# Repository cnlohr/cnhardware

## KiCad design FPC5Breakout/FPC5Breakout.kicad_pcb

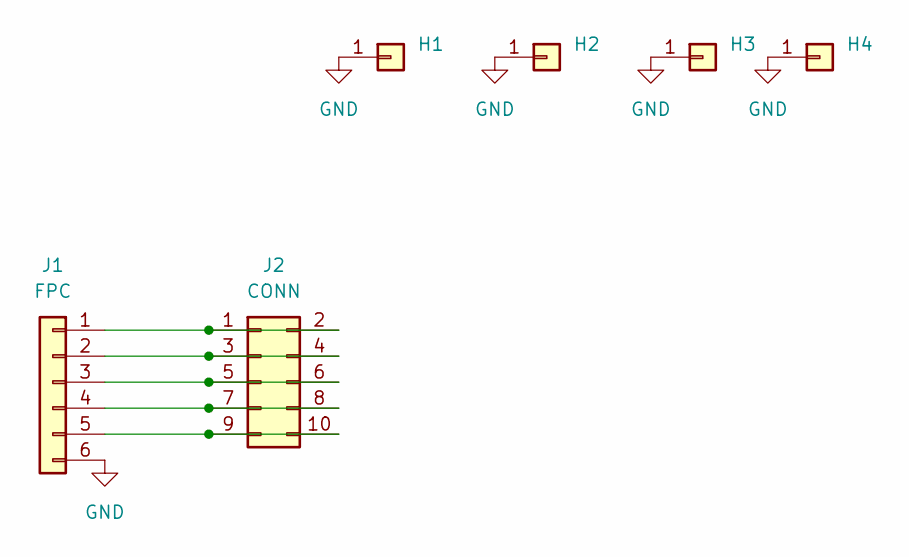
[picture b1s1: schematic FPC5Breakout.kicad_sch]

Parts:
H1, H2, H3, H4: MountingHole_3.2mm_M3_ISO14580_Pad
J1: FPC; XCB-FPC-DS-05-0.5mm; LCSC C2880762
J2: CONN; PinHeader_2x05_P2.54mm_Vertical; LCSC C124387

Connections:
GND: H1.1, H2.1, H3.1, H4.1, J1.6
unnamed: J1.1, J2.1, J2.2
unnamed: J1.2, J2.3, J2.4
unnamed: J1.3, J2.5, J2.6
unnamed: J1.4, J2.7, J2.8
unnamed: J1.5, J2.9, J2.10

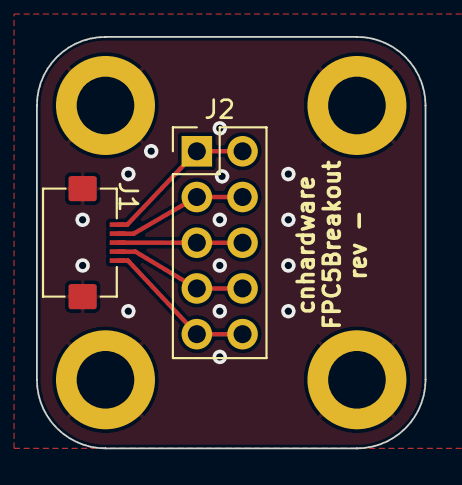
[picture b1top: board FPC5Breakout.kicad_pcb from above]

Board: 2 copper layers, 21.6 x 22.9 mm, 6 parts (0 on the bottom side), 6 nets.

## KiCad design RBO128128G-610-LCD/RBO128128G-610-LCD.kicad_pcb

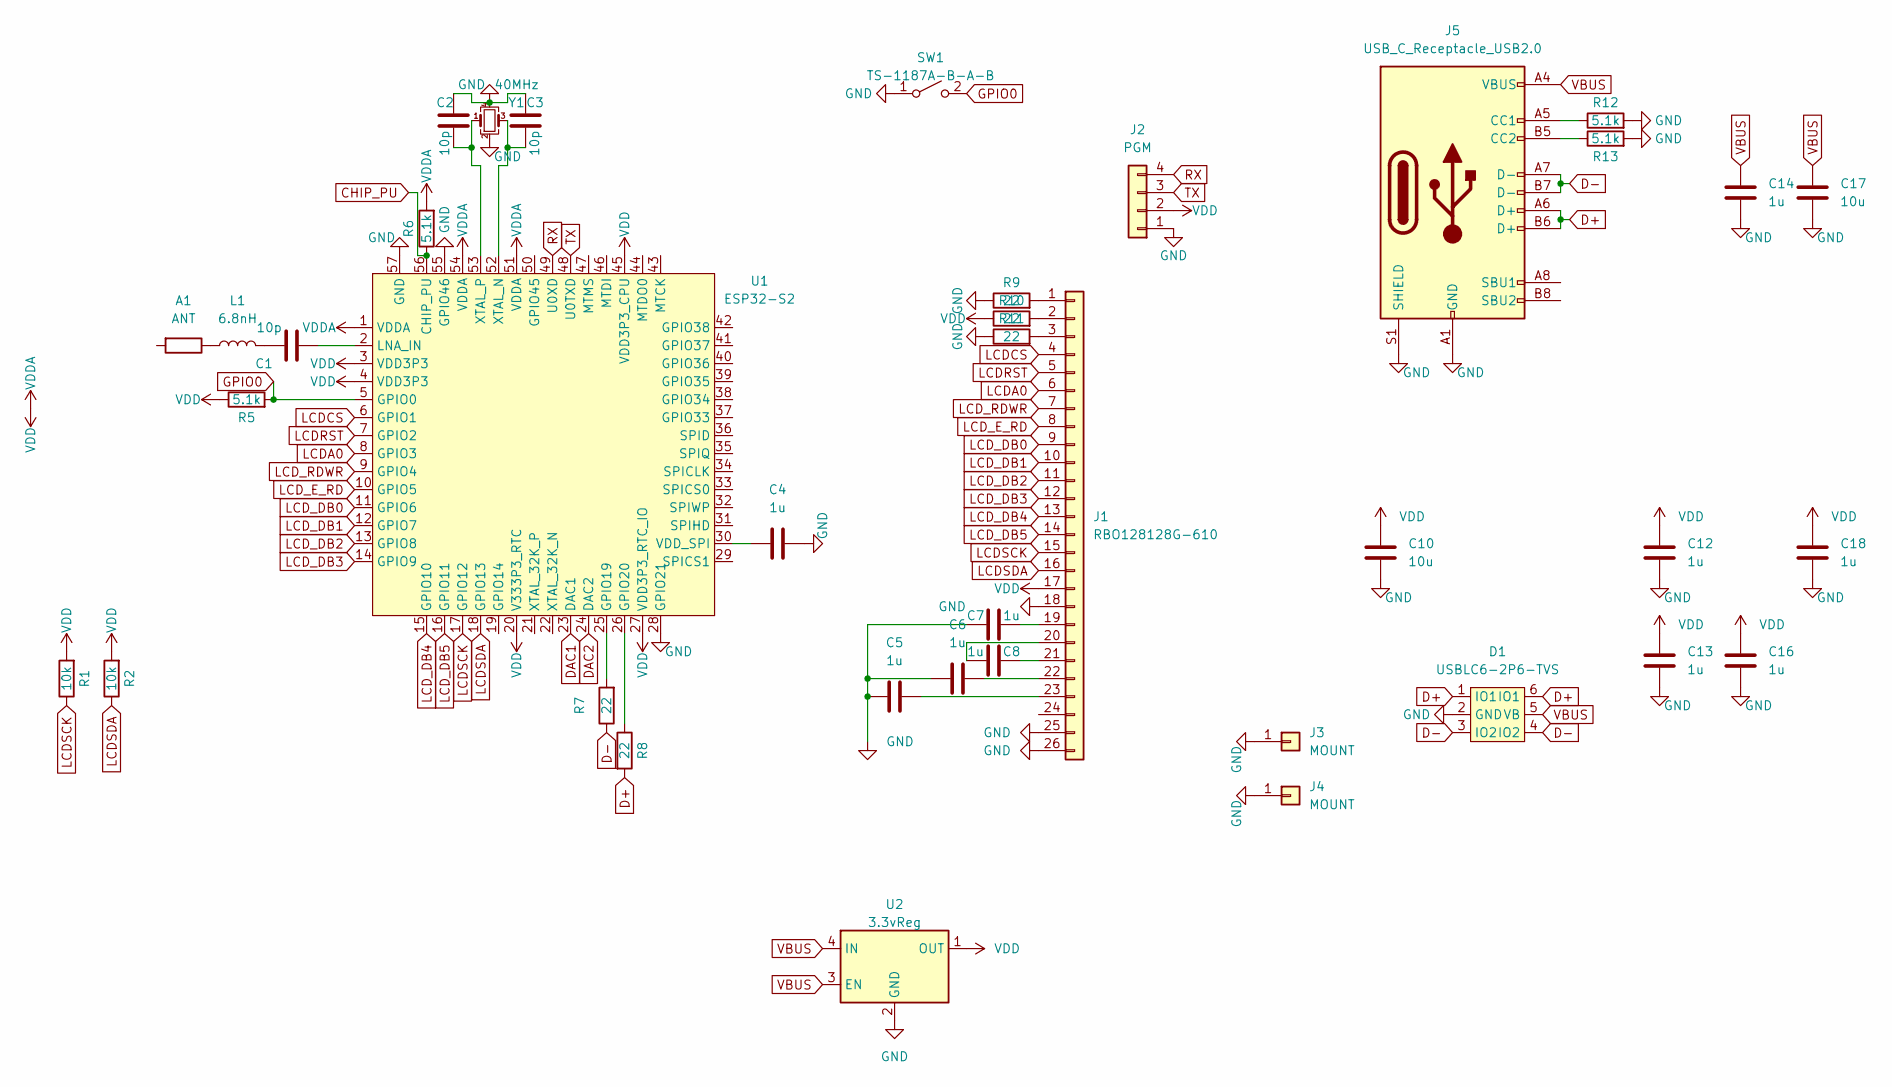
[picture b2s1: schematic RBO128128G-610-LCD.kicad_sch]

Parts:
A1: ANT; R_1206_3216Metric; LCSC C127629
C1, C2, C3: 10p; C_0402_1005Metric; LCSC C106199
C4, C5, C6, C7, C8, C12, C13, C14, C16, C18: 1u; C_0402_1005Metric; LCSC C106254
C10, C17: 10u; C_0603_1608Metric; LCSC C18800
D1: USBLC6-2P6-TVS; SOT-666; LCSC C2827693
J1: RBO128128G-610
J2: PGM; PinHeader_1x04_P2.54mm_Vertical; LCSC NP
J3, J4: MOUNT; MountingHole_2.2mm_M2_DIN965_Pad
J5: USB_C_Receptacle_USB2.0; USB_C_Receptacle_HRO_TYPE-C-31-M-12; LCSC C2765186
L1: 6.8nH; L_0402_1005Metric; LCSC C77110
R1, R2: 10k; R_0402_1005Metric; LCSC C144807
R5, R6, R12, R13: 5.1k; R_0402_1005Metric; LCSC C105872
R7, R8, R9, R10, R11: 22; R_0402_1005Metric; LCSC C25092
SW1: TS-1187A-B-A-B; SW_SPST_TL3342; LCSC C318884
U1: ESP32-S2; ESP32S2; LCSC C2840995
U2: 3.3vReg; xdfn-reg; LCSC C81114
Y1: 40MHz; Crystal_SMD_2016-4Pin_2.0x1.6mm; LCSC C648970

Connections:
CHIP_PU: R6.1, U1.56 (CHIP_PU)
D+: D1.1 (IO1), D1.6 (IO1), J5.A6 (D+), J5.B6 (D+), R8.2
D-: D1.3 (IO2), D1.4 (IO2), J5.A7 (D-), J5.B7 (D-), R7.1
DAC1: U1.23 (DAC1)
DAC2: U1.24 (DAC2)
GND: C2.1, C3.1, C4.2, C5.1, C6.1, C7.1, C10.2, C12.2, C13.2, C14.1, C16.2, C17.2, C18.2, D1.2 (GND), J1.18, J1.25, J1.26, J2.1, J3.1, J4.1, J5.A1 (GND), J5.A12 (GND), J5.B1 (GND), J5.B12 (GND), J5.S1 (SHIELD), R9.1, R11.1, R12.2, R13.2, SW1.1 (A), U1.28 (GPIO21), U1.55 (GPIO46), U1.57 (GND), U2.2 (GND), U2.5 (GND), Y1.2, Y1.4
GPIO0: R5.2, SW1.2 (B), U1.5 (GPIO0)
LCDA0: J1.6, U1.8 (GPIO3)
LCDCS: J1.4, U1.6 (GPIO1)
LCDRST: J1.5, U1.7 (GPIO2)
LCDSCK: J1.15, R1.1, U1.17 (GPIO12)
LCDSDA: J1.16, R2.1, U1.18 (GPIO13)
LCD_DB0: J1.9, U1.11 (GPIO6)
LCD_DB1: J1.10, U1.12 (GPIO7)
LCD_DB2: J1.11, U1.13 (GPIO8)
LCD_DB3: J1.12, U1.14 (GPIO9)
LCD_DB4: J1.13, U1.15 (GPIO10)
LCD_DB5: J1.14, U1.16 (GPIO11)
LCD_E_RD: J1.8, U1.10 (GPIO5)
LCD_RDWR: J1.7, U1.9 (GPIO4)
unnamed: A1.1, L1.1
unnamed: C1.1, L1.2
unnamed: C1.2, U1.2 (LNA_IN)
unnamed: C2.2, U1.53 (XTAL_P), Y1.1
unnamed: C3.2, U1.52 (XTAL_N), Y1.3
unnamed: C4.1, U1.30 (VDD_SPI)
unnamed: C5.2, J1.23
unnamed: C6.2, J1.22
unnamed: C7.2, J1.19
unnamed: C8.1, J1.20
unnamed: C8.2, J1.21
unnamed: J1.1, R9.2
unnamed: J1.2, R10.2
unnamed: J1.3, R11.2
unnamed: J5.A5 (CC1), R12.1
unnamed: J5.B5 (CC2), R13.1
unnamed: R7.2, U1.25 (GPIO19)
unnamed: R8.1, U1.26 (GPIO20)
RX: J2.4, U1.49 (U0XD)
TX: J2.3, U1.48 (U0TXD)
VBUS: C14.2, C17.1, D1.5 (VB), J5.A4 (VBUS), J5.A9 (VBUS), J5.B4 (VBUS), J5.B9 (VBUS), U2.3 (EN), U2.4 (IN)
VDD: C10.1, C12.1, C13.1, C16.1, C18.1, J1.17, J2.2, R1.2, R2.2, R5.1, R6.2, R10.1, U1.1 (VDDA), U1.3 (VDD3P3), U1.4 (VDD3P3), U1.20 (V333P3_RTC), U1.27 (VDD3P3_RTC_IO), U1.45 (VDD3P3_CPU), U1.51 (VDDA), U1.54 (VDDA), U2.1 (OUT)

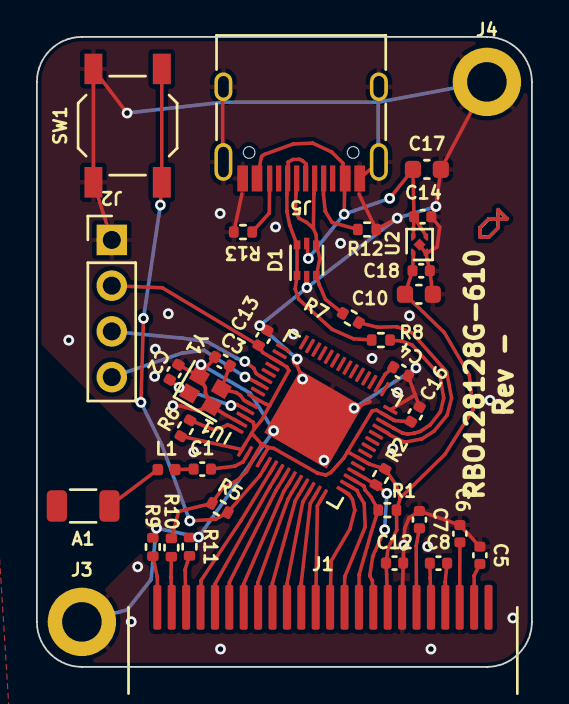
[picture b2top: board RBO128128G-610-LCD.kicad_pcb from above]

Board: 2 copper layers, 27.5 x 35.0 mm, 38 parts (0 on the bottom side), 40 nets.

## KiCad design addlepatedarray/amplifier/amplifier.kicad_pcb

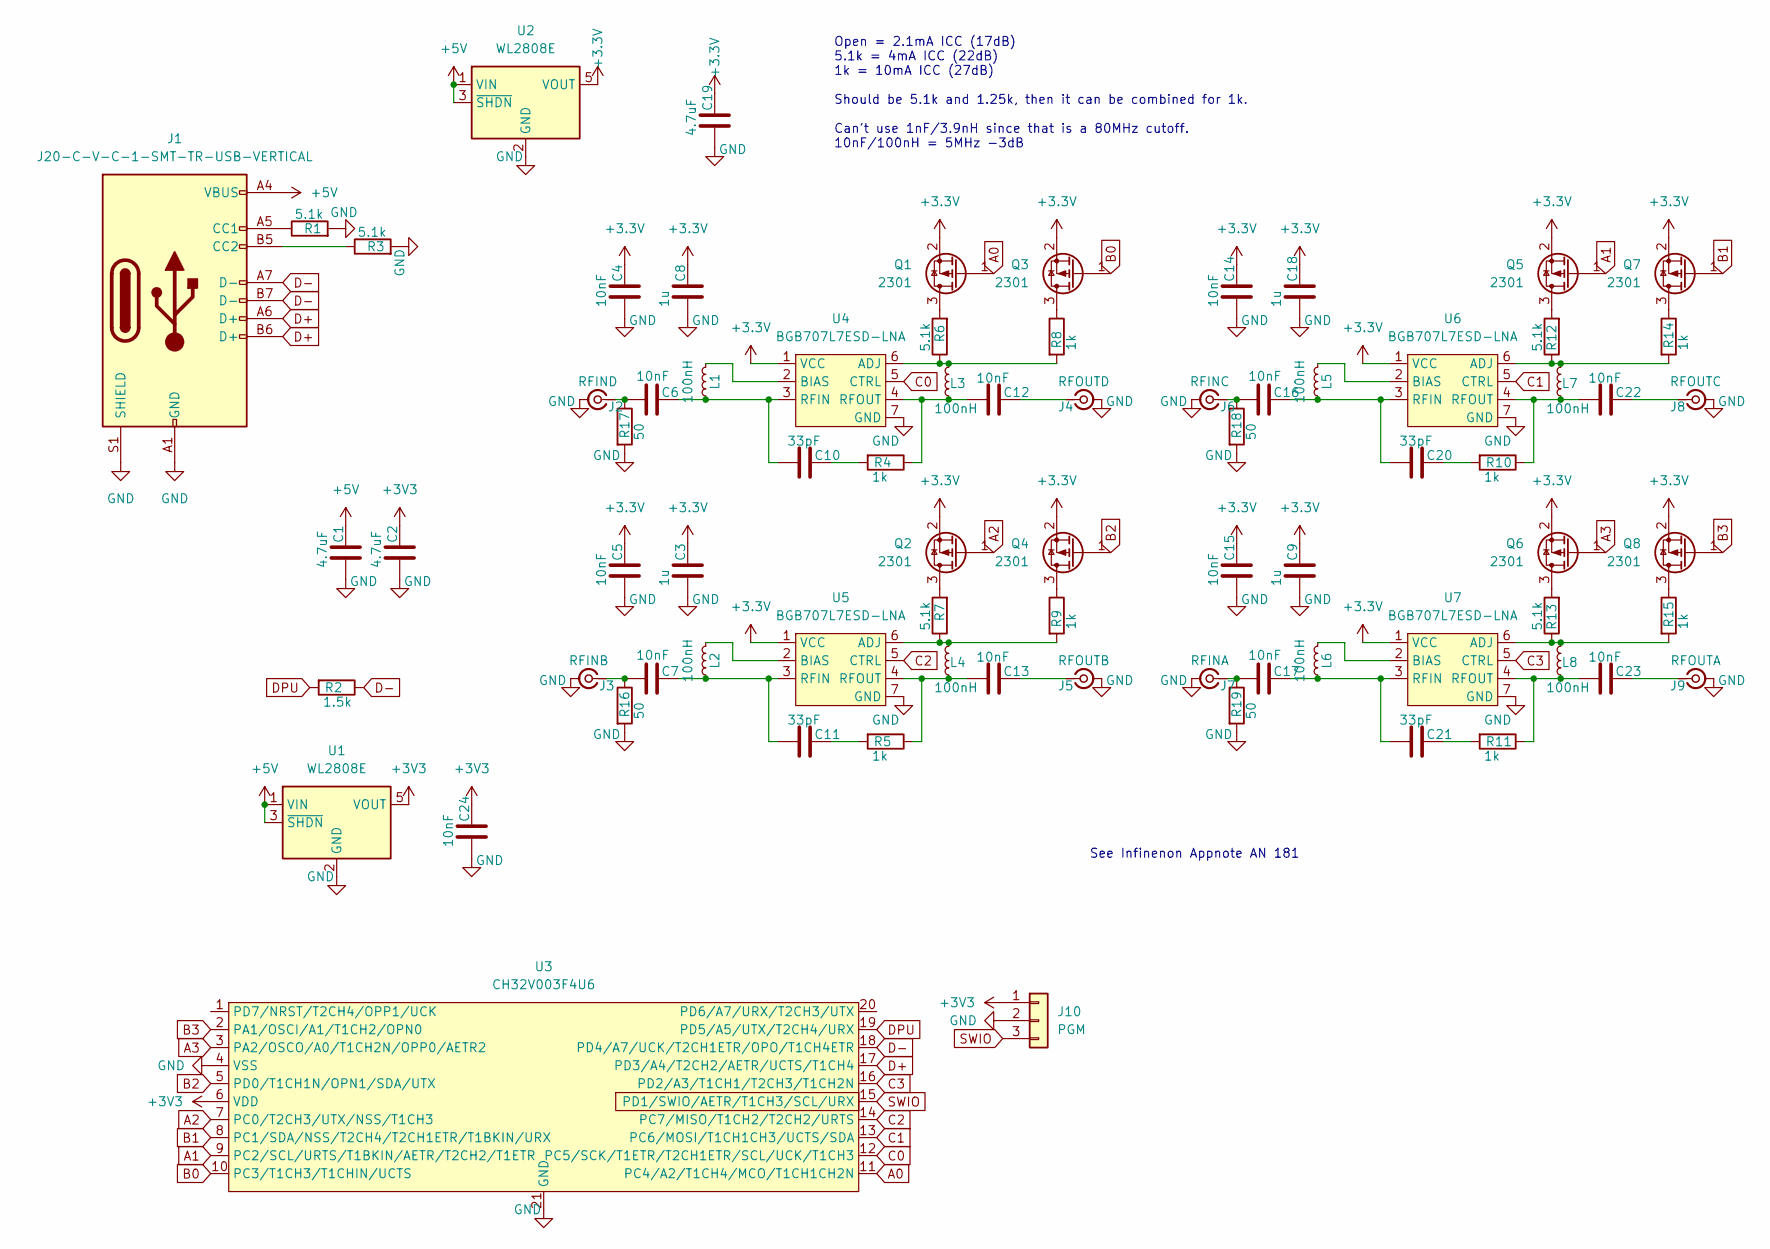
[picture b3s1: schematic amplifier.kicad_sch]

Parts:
C1, C2, C19: 4.7uF; R_0603_1608Metric; LCSC C19666
C3, C8, C9, C18: 1u; C_0402_1005Metric; LCSC C52923
C4, C5, C6, C7, C12, C13, C14, C15, C16, C17, C22, C23, C24: 10nF; C_0402_1005Metric; LCSC C15195
C10, C11, C20, C21: 33pF; C_0402_1005Metric; LCSC C1562
J1: J20-C-V-C-1-SMT-TR-USB-VERTICAL; LCSC NA
J2: RFIND; SMA_Amphenol_901-144_Vertical; LCSC C5301852
J3: RFINB; SMA_Amphenol_901-144_Vertical; LCSC C5301852
J4: RFOUTD; SMA_Amphenol_901-144_Vertical; LCSC C5301852
J5: RFOUTB; SMA_Amphenol_901-144_Vertical; LCSC C5301852
J6: RFINC; SMA_Amphenol_901-144_Vertical; LCSC C5301852
J7: RFINA; SMA_Amphenol_901-144_Vertical; LCSC C5301852
J8: RFOUTC; SMA_Amphenol_901-144_Vertical; LCSC C5301852
J9: RFOUTA; SMA_Amphenol_901-144_Vertical; LCSC C5301852
J10: PGM; PinHeader_1x03_P2.54mm_Vertical
L1, L2, L3, L4, L5, L6, L7, L8: 100nH; L_0402_1005Metric; LCSC C22726
Q1, Q2, Q3, Q4, Q5, Q6, Q7, Q8: 2301; SOT-23; LCSC C41384537
R1, R3, R6, R7, R12, R13: 5.1k; R_0402_1005Metric; LCSC C25905
R2: 1.5k; R_0402_1005Metric; LCSC C25867
R4, R5, R8, R9, R10, R11, R14, R15: 1k; R_0402_1005Metric; LCSC C11702
R16, R17, R18, R19: 50; R_0402_1005Metric; LCSC C25120
U1, U2: WL2808E; SOT-23-5; LCSC C2931312
U3: CH32V003F4U6; QFN-20-1EP_3x3mm_P0.4mm_EP1.65x1.65mm; LCSC C5299908
U4, U5, U6, U7: BGB707L7ESD-LNA; TSLP-7-1; LCSC C3199311

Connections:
+3.3V: C3.1, C4.1, C5.1, C8.1, C9.1, C14.1, C15.1, C18.1, C19.1, Q1.2 (S), Q2.2 (S), Q3.2 (S), Q4.2 (S), Q5.2 (S), Q6.2 (S), Q7.2 (S), Q8.2 (S), U2.5 (VOUT), U4.1 (VCC), U5.1 (VCC), U6.1 (VCC), U7.1 (VCC)
+3V3: C2.1, C24.1, J10.1, U1.5 (VOUT), U3.6 (VDD)
+5V: C1.1, J1.A4 (VBUS), J1.A9 (VBUS), J1.B4 (VBUS), J1.B9 (VBUS), U1.1 (VIN), U1.3 (~SHDN), U2.1 (VIN), U2.3 (~SHDN)
A0: Q1.1 (G), U3.11 (PC4/A2/T1CH4/MCO/T1CH1CH2N)
A1: Q5.1 (G), U3.9 (PC2/SCL/URTS/T1BKIN/AETR/T2CH2/T1ETR)
A2: Q2.1 (G), U3.7 (PC0/T2CH3/UTX/NSS/T1CH3)
A3: Q6.1 (G), U3.3 (PA2/OSCO/A0/T1CH2N/OPP0/AETR2)
B0: Q3.1 (G), U3.10 (PC3/T1CH3/T1CHIN/UCTS)
B1: Q7.1 (G), U3.8 (PC1/SDA/NSS/T2CH4/T2CH1ETR/T1BKIN/URX)
B2: Q4.1 (G), U3.5 (PD0/T1CH1N/OPN1/SDA/UTX)
B3: Q8.1 (G), U3.2 (PA1/OSCI/A1/T1CH2/OPN0)
C0: U3.12 (PC5/SCK/T1ETR/T2CH1ETR/SCL/UCK/T1CH3), U4.5 (CTRL)
C1: U3.13 (PC6/MOSI/T1CH1CH3/UCTS/SDA), U6.5 (CTRL)
C2: U3.14 (PC7/MISO/T1CH2/T2CH2/URTS), U5.5 (CTRL)
C3: U3.16 (PD2/A3/T1CH1/T2CH3/T1CH2N), U7.5 (CTRL)
D+: J1.A6 (D+), J1.B6 (D+), U3.17 (PD3/A4/T2CH2/AETR/UCTS/T1CH4)
D-: J1.A7 (D-), J1.B7 (D-), R2.1, U3.18 (PD4/A7/UCK/T2CH1ETR/OPO/T1CH4ETR)
DPU: R2.2, U3.19 (PD5/A5/UTX/T2CH4/URX)
GND: C1.2, C2.2, C3.2, C4.2, C5.2, C8.2, C9.2, C14.2, C15.2, C18.2, C19.2, C24.2, J1.A1 (GND), J1.A12 (GND), J1.B1 (GND), J1.B12 (GND), J1.S1 (SHIELD), J2.2 (Ext), J3.2 (Ext), J4.2 (Ext), J5.2 (Ext), J6.2 (Ext), J7.2 (Ext), J8.2 (Ext), J9.2 (Ext), J10.2, R1.2, R3.2, R16.2, R17.2, R18.2, R19.2, U1.2 (GND), U2.2 (GND), U3.4 (VSS), U3.21 (GND), U4.7 (GND), U5.7 (GND), U6.7 (GND), U7.7 (GND)
unnamed: C10.1, R4.2
unnamed: C11.1, R5.2
unnamed: C20.1, R10.2
unnamed: C21.1, R11.2
unnamed: J1.A5 (CC1), R1.1
unnamed: J1.B5 (CC2), R3.1
unnamed: C6.2, J2.1 (In), R17.1
unnamed: C7.2, J3.1 (In), R16.1
unnamed: C12.1, J4.1 (In)
unnamed: C13.1, J5.1 (In)
unnamed: C16.2, J6.1 (In), R18.1
unnamed: C17.2, J7.1 (In), R19.1
unnamed: C22.1, J8.1 (In)
unnamed: C23.1, J9.1 (In)
unnamed: Q1.3 (D), R6.2
unnamed: Q2.3 (D), R7.2
unnamed: Q3.3 (D), R8.1
unnamed: Q4.3 (D), R9.1
unnamed: Q5.3 (D), R12.2
unnamed: Q6.3 (D), R13.2
unnamed: Q7.3 (D), R14.1
unnamed: Q8.3 (D), R15.1
unnamed: L3.2, R6.1, R8.2, U4.6 (ADJ)
unnamed: L1.2, U4.2 (BIAS)
unnamed: C6.1, C10.2, L1.1, U4.3 (RFIN)
unnamed: C12.2, L3.1, R4.1, U4.4 (RFOUT)
unnamed: L4.2, R7.1, R9.2, U5.6 (ADJ)
unnamed: L2.2, U5.2 (BIAS)
unnamed: C7.1, C11.2, L2.1, U5.3 (RFIN)
unnamed: C13.2, L4.1, R5.1, U5.4 (RFOUT)
unnamed: L7.2, R12.1, R14.2, U6.6 (ADJ)
unnamed: L5.2, U6.2 (BIAS)
unnamed: C16.1, C20.2, L5.1, U6.3 (RFIN)
unnamed: C22.2, L7.1, R10.1, U6.4 (RFOUT)
unnamed: L8.2, R13.1, R15.2, U7.6 (ADJ)
unnamed: L6.2, U7.2 (BIAS)
unnamed: C17.1, C21.2, L6.1, U7.3 (RFIN)
unnamed: C23.2, L8.1, R11.1, U7.4 (RFOUT)
SWIO: J10.3, U3.15 (PD1/SWIO/AETR/T1CH3/SCL/URX)

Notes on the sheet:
Open = 2.1mA ICC (17dB) 5.1k = 4mA ICC (22dB) 1k = 10mA ICC (27dB) Should be 5.1k and 1.25k, then it can be combined for 1k. Can't use 1nF/3.9nH since that is a 80MHz cutoff. 10nF/100nH = 5MHz -3dB
See Infinenon Appnote AN 181

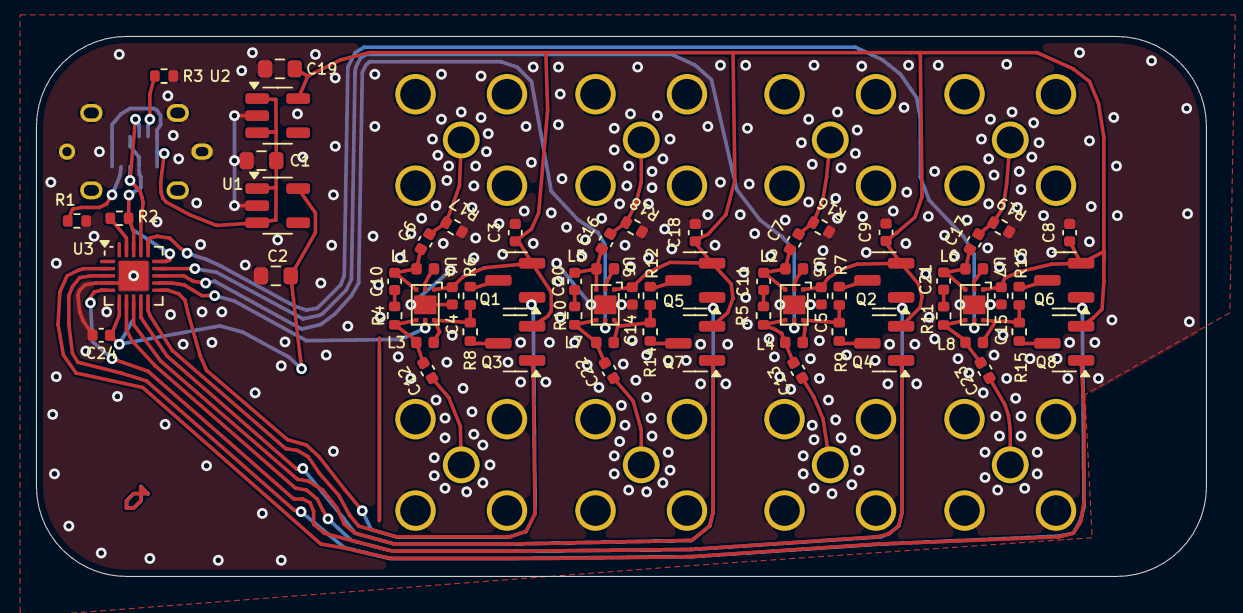
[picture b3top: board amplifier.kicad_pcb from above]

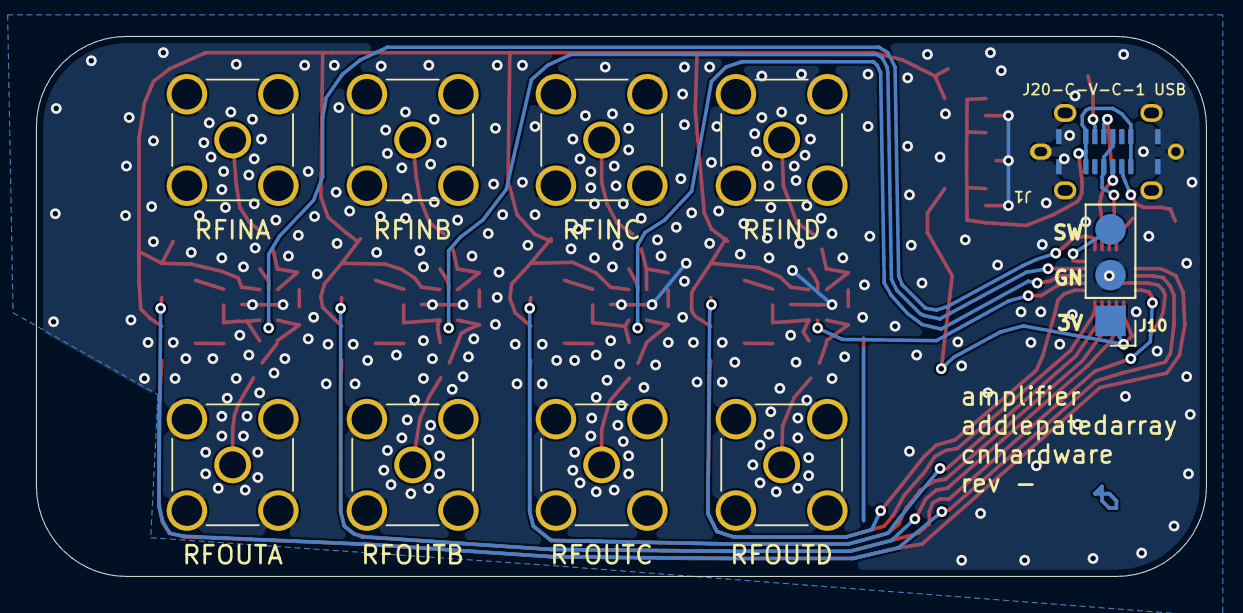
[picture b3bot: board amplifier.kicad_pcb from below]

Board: 2 copper layers, 65.0 x 30.0 mm, 76 parts (10 on the bottom side), 58 nets.

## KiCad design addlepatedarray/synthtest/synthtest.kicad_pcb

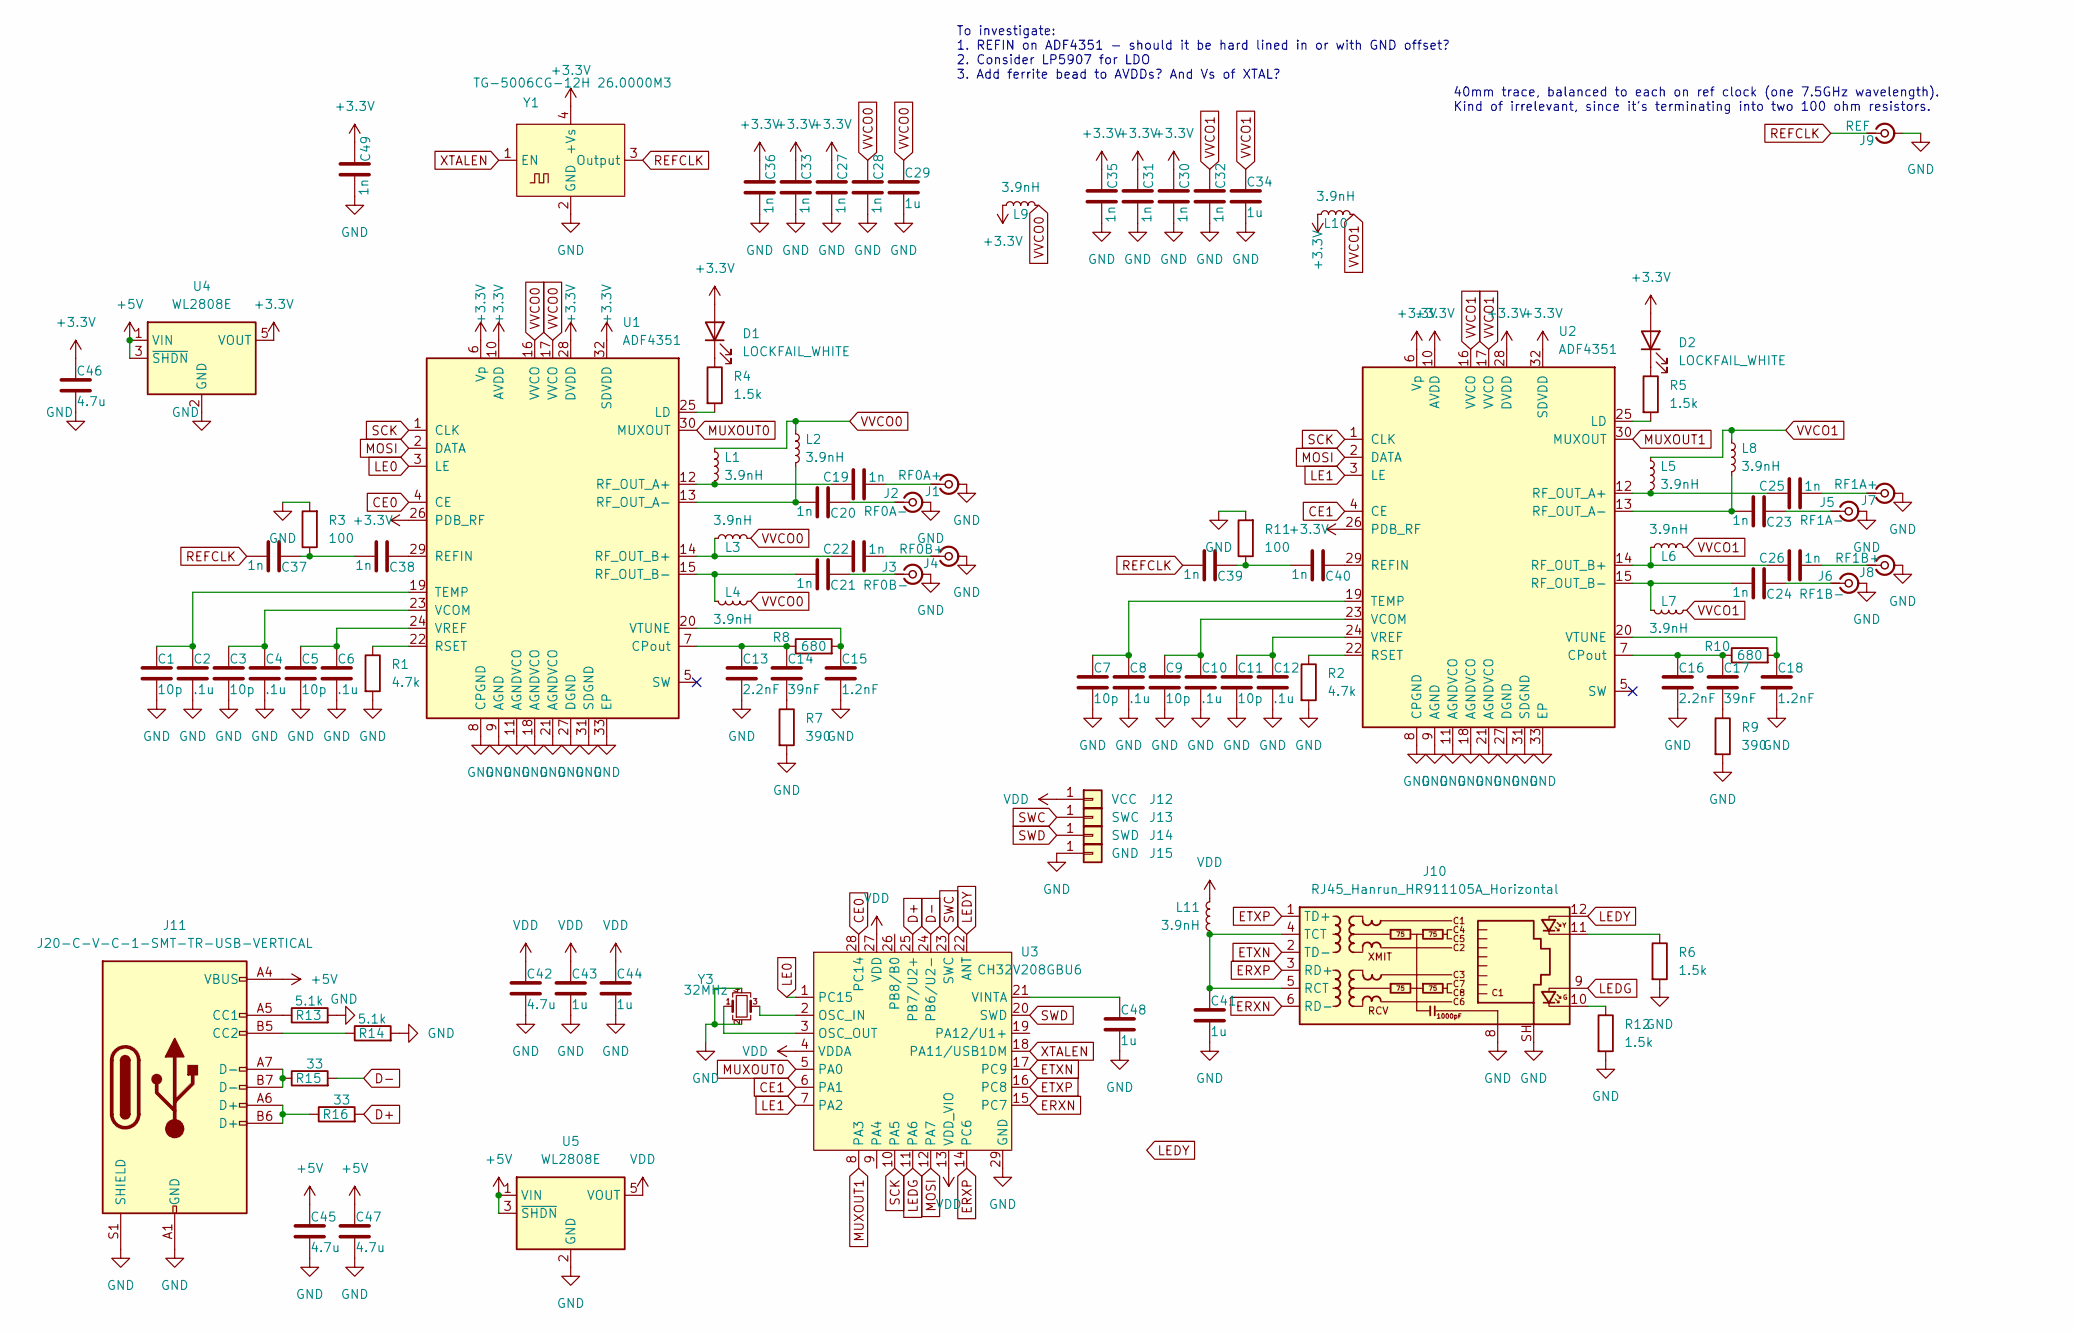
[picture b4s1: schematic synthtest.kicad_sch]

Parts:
C1, C3, C5, C7, C9, C11: 10p; C_0402_1005Metric; LCSC C32949
C2, C4, C6, C8, C10, C12: .1u; C_0402_1005Metric; LCSC C1525
C13, C16: 2.2nF; C_0402_1005Metric; LCSC C22435967
C14, C17: 39nF; C_0402_1005Metric; LCSC C880624
C15, C18: 1.2nF; C_0402_1005Metric; LCSC C107021
C19, C20, C21, C22, C23, C24, C25, C26, C27, C28, C30, C31, C32, C33, C35, C36, C37, C38, C39, C40, C49: 1n; C_0402_1005Metric; LCSC C1523
C29, C34, C41, C43, C44, C48: 1u; C_0402_1005Metric; LCSC C14445
C42, C45, C46, C47: 4.7u; C_0603_1608Metric; LCSC C19666
D1, D2: LOCKFAIL_WHITE; LED_0603_1608Metric; LCSC C2290
J1: RF0A+; SMA_Amphenol_901-144_Vertical; LCSC C5301852
J2: RF0A-; SMA_Amphenol_901-144_Vertical; LCSC C5301852
J3: RF0B-; SMA_Amphenol_901-144_Vertical; LCSC C5301852
J4: RF0B+; SMA_Amphenol_901-144_Vertical; LCSC C5301852
J5: RF1A-; SMA_Amphenol_901-144_Vertical; LCSC C5301852
J6: RF1B-; SMA_Amphenol_901-144_Vertical; LCSC C5301852
J7: RF1A+; SMA_Amphenol_901-144_Vertical; LCSC C5301852
J8: RF1B+; SMA_Amphenol_901-144_Vertical; LCSC C5301852
J9: REF; SMA_Amphenol_901-144_Vertical; LCSC C5301852
J10: RJ45_Hanrun_HR911105A_Horizontal; HR915310A-RJ45-INTEGRATED-10MBIT; LCSC C2760326
J11: J20-C-V-C-1-SMT-TR-USB-VERTICAL
J12: VCC; TestPoint_Pad_D1.0mm
J13: SWC; TestPoint_Pad_D1.0mm
J14: SWD; TestPoint_Pad_D1.0mm
J15: GND; TestPoint_Pad_D1.0mm
L1, L2, L3, L4, L5, L6, L7, L8, L9, L10, L11: 3.9nH; L_0402_1005Metric; LCSC C77109
R1, R2: 4.7k; R_0402_1005Metric_COMPACT; LCSC C25900
R3, R11: 100; R_0402_1005Metric; LCSC C25076
R4, R5, R6, R12: 1.5k; R_0402_1005Metric_COMPACT; LCSC C25867
R7, R9: 390; R_0402_1005Metric; LCSC C25109
R8, R10: 680; R_0402_1005Metric; LCSC C25109
R13, R14: 5.1k; R_0402_1005Metric; LCSC C25905
R15, R16: 33; R_0402_1005Metric; LCSC C25105
U1, U2: ADF4351; LFCSP-32-1EP_5x5mm_P0.5mm_EP3.25x3.25mm; LCSC C71362
U3: CH32V208GBU6; QFN-28-P0.4mm-2.8x2.8EP; LCSC C7434833
U4, U5: WL2808E; SOT-23-5; LCSC C2931312
Y1: TG-5006CG-12H 26.0000M3; Oscillator_SMD_ECS_2520MV-xxx-xx-4Pin_2.5x2.0mm; LCSC C1998253
Y3: 32MHz; Crystal_SMD_2016-4Pin_2.0x1.6mm; LCSC C37635331

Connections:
+5V: C45.1, C47.1, J11.A4 (VBUS), J11.A9 (VBUS), J11.B4 (VBUS), J11.B9 (VBUS), U4.1 (VIN), U4.3 (~SHDN), U5.1 (VIN), U5.3 (~SHDN)
CE0: U1.4 (CE), U3.28 (PC14)
CE1: U2.4 (CE), U3.6 (PA1)
D+: R16.2, U3.25 (PB7/U2+)
D-: R15.2, U3.24 (PB6/U2-)
ERXN: J10.6 (RD-), U3.15 (PC7)
ERXP: J10.3 (RD+), U3.14 (PC6)
ETXN: J10.2 (TD-), U3.17 (PC9)
ETXP: J10.1 (TD+), U3.16 (PC8)
LE0: U1.3 (LE), U3.1 (PC15)
LE1: U2.3 (LE), U3.7 (PA2)
LEDG: J10.9, U3.11 (PA6)
LEDY: J10.12, U3.22 (ANT)
MOSI: U1.2 (DATA), U2.2 (DATA), U3.12 (PA7)
MUXOUT0: U1.30 (MUXOUT), U3.5 (PA0)
MUXOUT1: U2.30 (MUXOUT), U3.8 (PA3)
unnamed: C14.2, R7.1
unnamed: C17.2, R9.1
unnamed: C37.2, C38.1, R3.1
unnamed: C39.2, C40.1, R11.1
unnamed: D1.1 (K), R4.1
unnamed: D2.1 (K), R5.1
unnamed: C19.2, J1.1 (In)
unnamed: C20.2, J2.1 (In)
unnamed: C21.2, J3.1 (In)
unnamed: C22.2, J4.1 (In)
unnamed: C23.2, J5.1 (In)
unnamed: C24.2, J6.1 (In)
unnamed: C25.2, J7.1 (In)
unnamed: C26.2, J8.1 (In)
unnamed: J10.10, R12.1
unnamed: J10.11, R6.1
unnamed: C41.1, J10.4 (TCT), J10.5 (RCT), L11.2
unnamed: J11.A5 (CC1), R13.1
unnamed: J11.B5 (CC2), R14.1
unnamed: J11.A6 (D+), J11.B6 (D+), R16.1
unnamed: J11.A7 (D-), J11.B7 (D-), R15.1
unnamed: C13.1, C14.1, R8.1, U1.7 (CPout)
unnamed: R4.2, U1.25 (LD)
unnamed: C38.2, U1.29 (REFIN)
unnamed: C19.1, L1.2, U1.12 (RF_OUT_A+)
unnamed: C20.1, L2.2, U1.13 (RF_OUT_A-)
unnamed: C22.1, L3.1, U1.14 (RF_OUT_B+)
unnamed: C21.1, L4.1, U1.15 (RF_OUT_B-)
unnamed: R1.1, U1.22 (RSET)
unnamed: C1.1, C2.1, U1.19 (TEMP)
unnamed: C3.1, C4.1, U1.23 (VCOM)
unnamed: C5.1, C6.1, U1.24 (VREF)
unnamed: C15.1, R8.2, U1.20 (VTUNE)
unnamed: C16.1, C17.1, R10.1, U2.7 (CPout)
unnamed: R5.2, U2.25 (LD)
unnamed: C40.2, U2.29 (REFIN)
unnamed: C25.1, L5.2, U2.12 (RF_OUT_A+)
unnamed: C23.1, L8.2, U2.13 (RF_OUT_A-)
unnamed: C26.1, L6.1, U2.14 (RF_OUT_B+)
unnamed: C24.1, L7.1, U2.15 (RF_OUT_B-)
unnamed: R2.1, U2.22 (RSET)
unnamed: C7.1, C8.1, U2.19 (TEMP)
unnamed: C9.1, C10.1, U2.23 (VCOM)
unnamed: C11.1, C12.1, U2.24 (VREF)
unnamed: C18.1, R10.2, U2.20 (VTUNE)
unnamed: U3.2 (OSC_IN), Y3.3
unnamed: U3.3 (OSC_OUT), Y3.1
unnamed: C48.1, U3.21 (VINTA)
REFCLK: C37.1, C39.1, J9.1 (In), Y1.3 (Output)
SCK: U1.1 (CLK), U2.1 (CLK), U3.10 (PA5)
SWC: J13.1, U3.23 (SWC)
SWD: J14.1, U3.20 (SWD)
VDD: C42.1, C43.1, C44.1, J12.1, L11.1, U3.4 (VDDA), U3.13 (VDD_VIO), U3.27 (VDD), U5.5 (VOUT)
VVCO0: C28.2, C29.1, L1.1, L2.1, L3.2, L4.2, L9.2, U1.16 (VVCO), U1.17 (VVCO)
VVCO1: C32.2, C34.1, L5.1, L6.2, L7.2, L8.1, L10.2, U2.16 (VVCO), U2.17 (VVCO)
XTALEN: U3.18 (PA11/USB1DM), Y1.1 (EN)

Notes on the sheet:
40mm trace, balanced to each on ref clock (one 7.5GHz wavelength). Kind of irrelevant, since it's terminating into two 100 ohm resistors.
To investigate: 1. REFIN on ADF4351 - should it be hard lined in or with GND offset? 2. Consider LP5907 for LDO 3. Add ferrite bead to AVDDs? And Vs of XTAL?

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
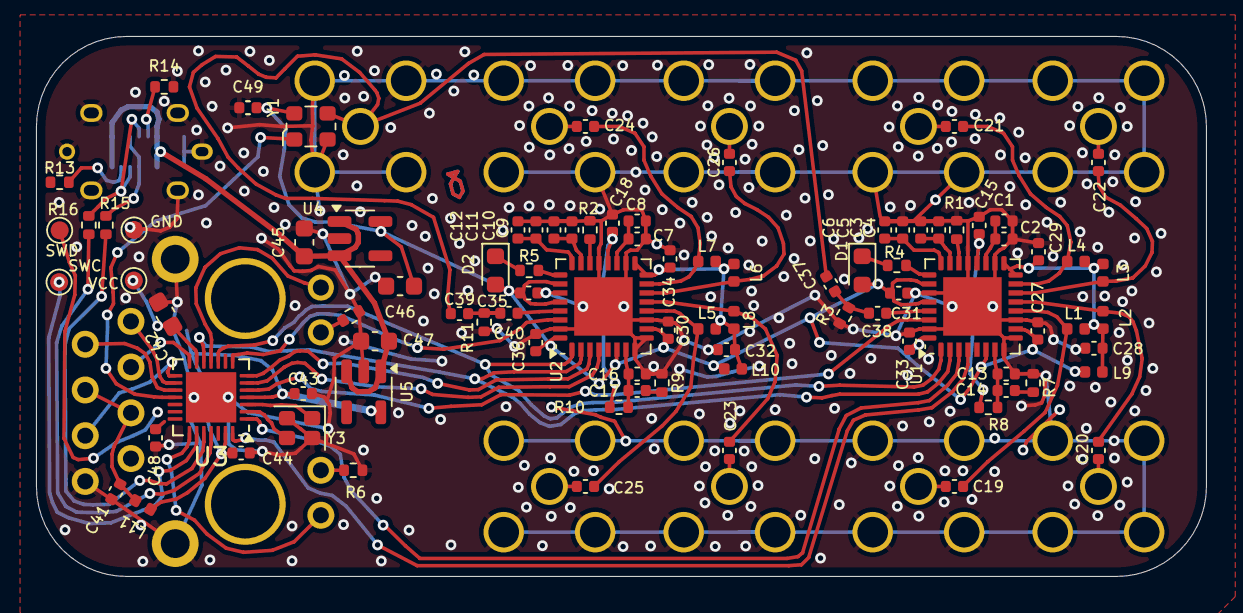
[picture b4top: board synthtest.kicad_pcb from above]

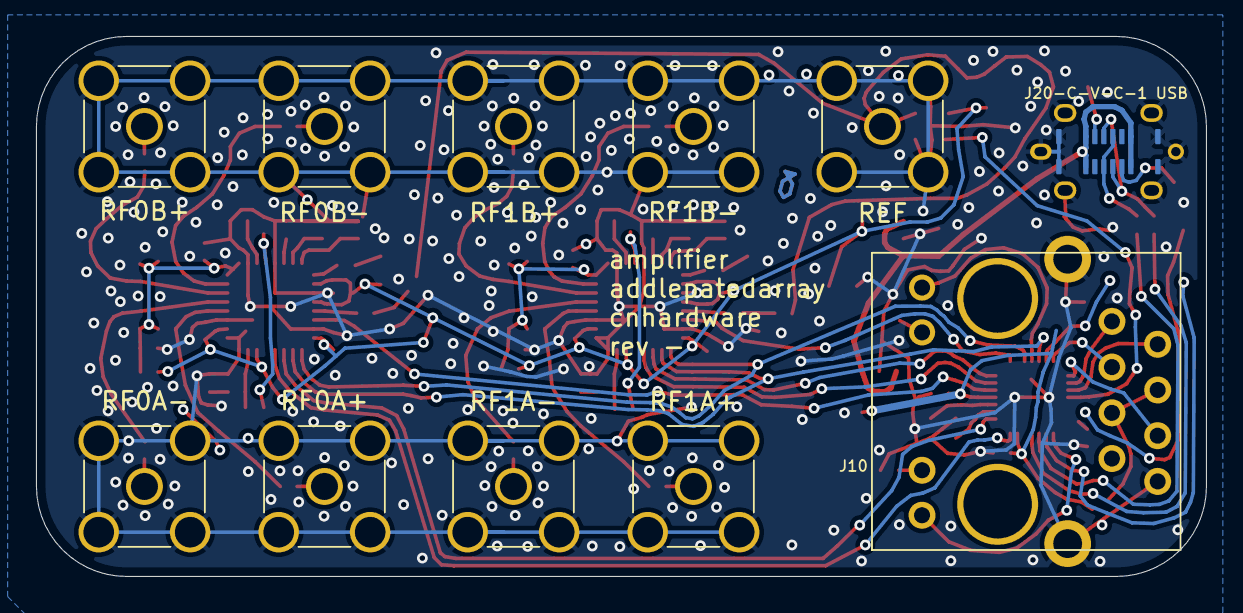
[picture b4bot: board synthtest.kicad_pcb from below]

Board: 2 copper layers, 65.0 x 30.0 mm, 100 parts (11 on the bottom side), 74 nets.

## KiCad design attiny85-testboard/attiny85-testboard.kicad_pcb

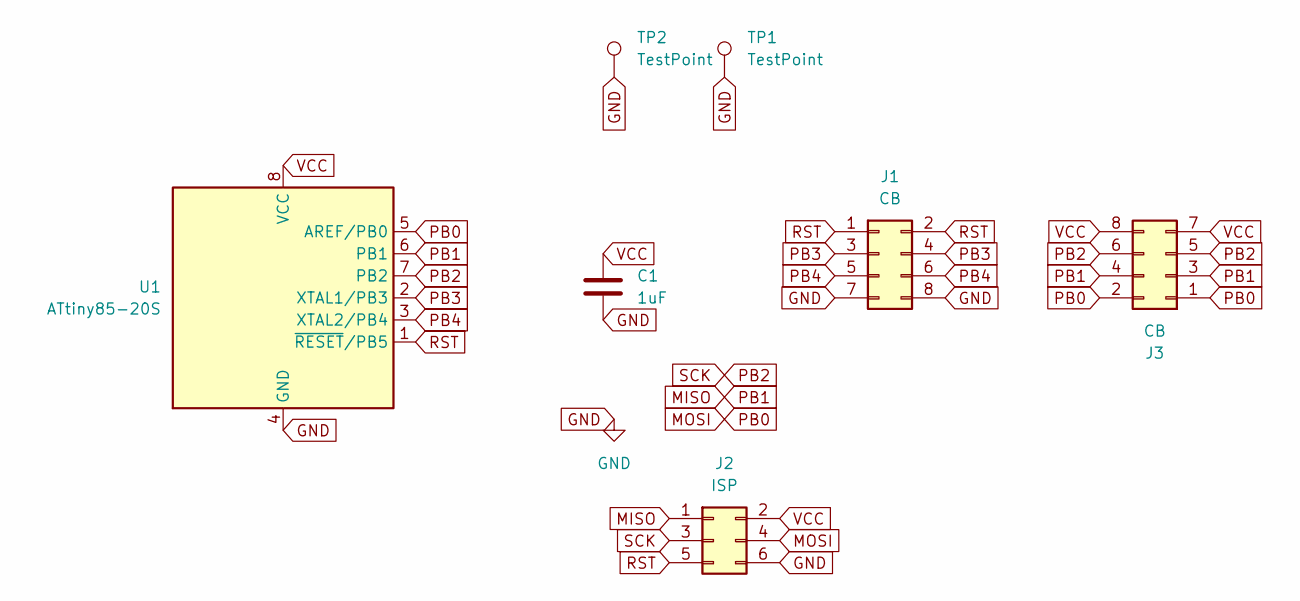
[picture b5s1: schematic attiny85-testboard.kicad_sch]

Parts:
C1: 1uF; C_0805_2012Metric; LCSC C28323
J1, J3: CB; PinHeader_2x04_P2.54mm_Vertical_SMD; LCSC C192300
J2: ISP; PinHeader_2x03_P2.54mm_Vertical_SMD; LCSC C192301
TP1, TP2: TestPoint; MountingHole_2.2mm_M2_DIN965_Pad
U1: ATtiny85-20S; SOIC-8W_5.3x5.3mm_P1.27mm; LCSC C615549

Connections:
GND: C1.2, J1.7, J1.8, J2.6, TP1.1, TP2.1, U1.4 (GND)
MISO: J2.1, J3.3, J3.4, U1.6 (PB1)
MOSI: J2.4, J3.1, J3.2, U1.5 (AREF/PB0)
PB2: J2.3, J3.5, J3.6, U1.7 (PB2)
PB3: J1.3, J1.4, U1.2 (XTAL1/PB3)
PB4: J1.5, J1.6, U1.3 (XTAL2/PB4)
RST: J1.1, J1.2, J2.5, U1.1 (~RESET/PB5)
VCC: C1.1, J2.2, J3.7, J3.8, U1.8 (VCC)

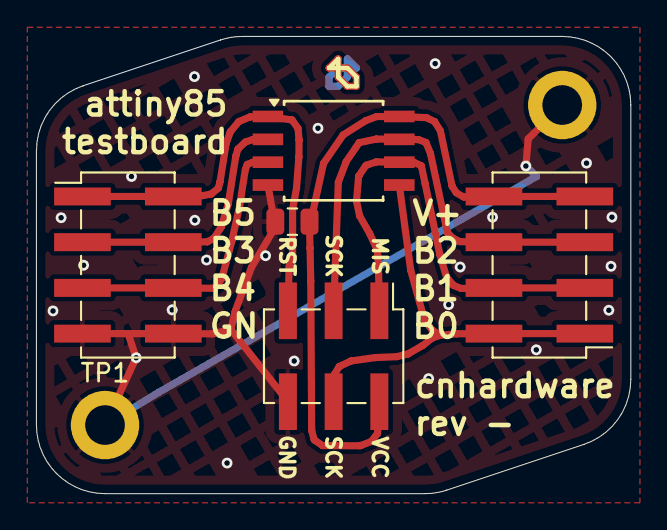
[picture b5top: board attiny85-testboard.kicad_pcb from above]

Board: 2 copper layers, 33.0 x 25.4 mm, 7 parts (0 on the bottom side), 8 nets.
